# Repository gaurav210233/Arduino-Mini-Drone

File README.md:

# Arduino-Mini-Drone

## Breakout Boards
* Arduino Pro Mini ATMEGA328P 5V/16M - https://robu.in/product/atmega328p-pro-mini-5v-16mhz-compatible-with-arduino/
* GY-91 MPU9250+BMP280 10DOF Acceleration Gyro 9-Axis Sensor Module - https://robu.in/product/gy-91-mpu9250bmp280-10dof-acceleration-gyro-9-axis-sensor-module/
* M177 NRF24L01 2.4GHz Antenna Wireless Transceiver Module - https://robu.in/product/m177-nrf24l01-2-4ghz-antenna-wireless-transceiver-module/

## Libraries
* Bolder Flight Systems MPU9250 - https://github.com/bolderflight/invensense-imu
* Adafruit_BMP280_Library - https://github.com/adafruit/Adafruit_BMP280_Library
* RF24 - https://github.com/nRF24/RF24

## Useful Links
* Interactive BOM V2 - https://gaurav210233.github.io/Arduino-Mini-Drone/Arduino-Mini-Drone-KiCad/V2/bom/ibom.html
* Interactive BOM V2-ESC - https://gaurav210233.github.io/Arduino-Mini-Drone/Arduino-Mini-Drone-KiCad/V2-ESC/bom/ibom.html
* Interactive BOM V2-FC - https://gaurav210233.github.io/Arduino-Mini-Drone/Arduino-Mini-Drone-KiCad/V2-FC/bom/ibom.html

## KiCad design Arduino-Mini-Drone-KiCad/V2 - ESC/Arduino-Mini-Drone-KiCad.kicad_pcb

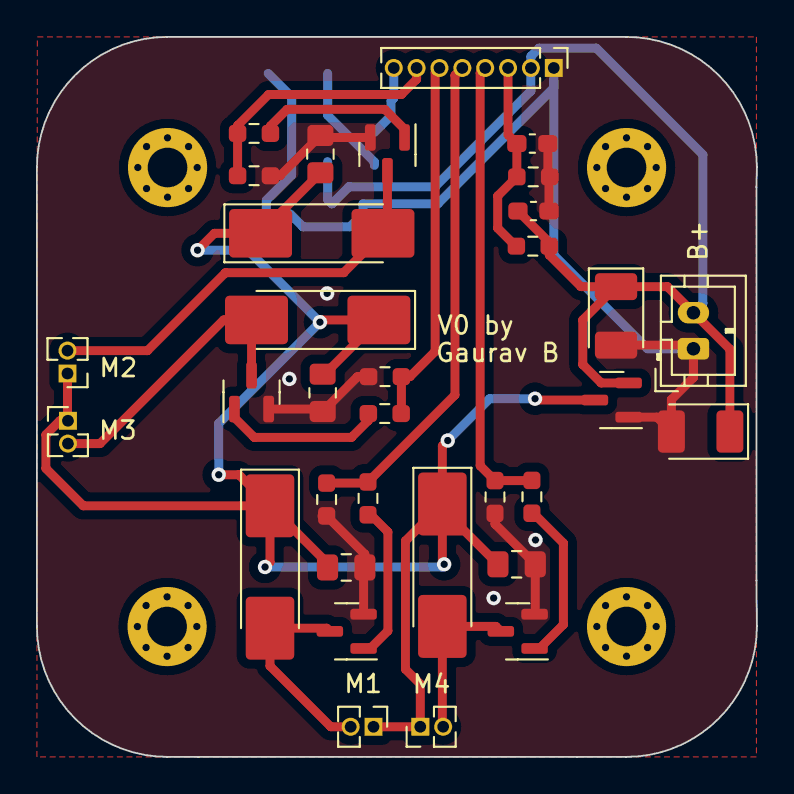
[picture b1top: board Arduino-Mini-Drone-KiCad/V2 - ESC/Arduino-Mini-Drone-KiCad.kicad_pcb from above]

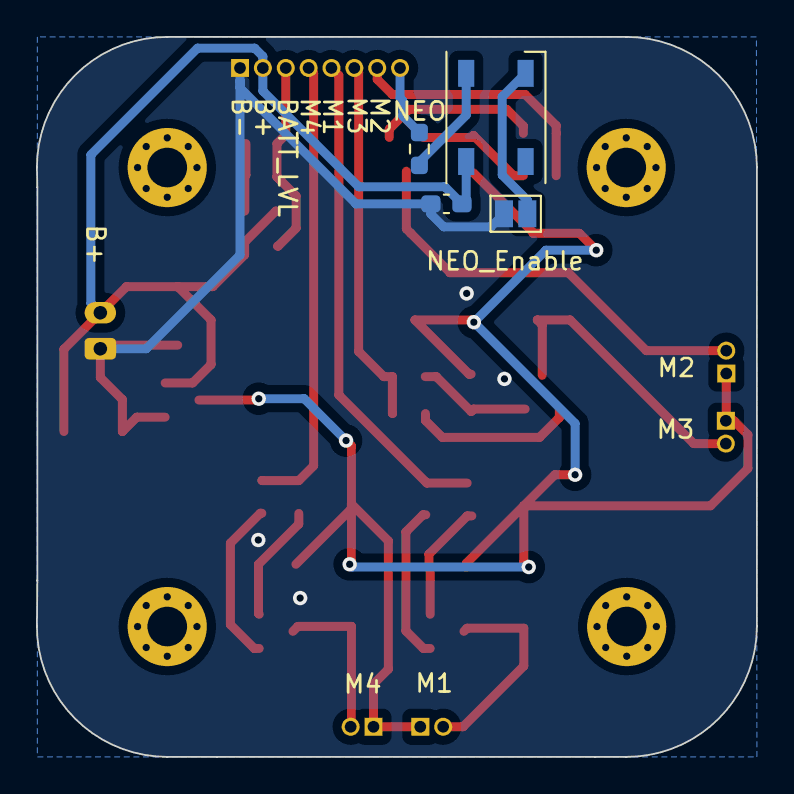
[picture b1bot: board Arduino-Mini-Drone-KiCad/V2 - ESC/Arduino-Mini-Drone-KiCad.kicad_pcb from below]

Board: 2 copper layers, 40.0 x 40.0 mm, 41 parts (4 on the bottom side), 19 nets.

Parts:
B+: PWR; JST_PH_B2B-PH-K_1x02_P2.00mm_Vertical
C10, C11, C12, C13: 22uf; C_0805_2012Metric_Pad1.18x1.45mm_HandSolder
C14, C15: 100uf; CP_EIA-3528-12_Kemet-T_Pad1.50x2.35mm_HandSolder
C17: 10uf; C_0603_1608Metric_Pad1.08x0.95mm_HandSolder
C18, C19: 100nf; C_0603_1608Metric_Pad1.08x0.95mm_HandSolder
D3, D4, D5, D6: SS34; D_MELF_Handsoldering
D9: WS2812B; LED_WS2812B_PLCC4_5.0x5.0mm_P3.2mm
H5, H6, H7, H8: MountingHole; MountingHole_2.2mm_M2_Pad_Via
M1: Motor1; PinHeader_1x02_P1.27mm_Vertical
M2: Motor2; PinHeader_1x02_P1.27mm_Vertical
M3: Motor3; PinHeader_1x02_P1.27mm_Vertical
M4: Motor4; PinHeader_1x02_P1.27mm_Vertical
NEO: POWER; PinHeader_1x08_P1.27mm_Vertical
NEO_Enable: LED ON OFF; SolderJumper-2_P1.3mm_Open_Pad1.0x1.5mm
Q1, Q2, Q3, Q4: AO3400A; SOT-23
Q5: AO3401A; SOT-23
R4, R6, R8, R10: 10k; R_0603_1608Metric_Pad0.98x0.95mm_HandSolder
R5, R7, R9, R11: 100; R_0603_1608Metric_Pad0.98x0.95mm_HandSolder
R12: 100k; R_0603_1608Metric_Pad0.98x0.95mm_HandSolder
R13: 33k; R_0603_1608Metric_Pad0.98x0.95mm_HandSolder
R14: 390; R_0603_1608Metric_Pad0.98x0.95mm_HandSolder

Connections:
+BATT: B+.2, C14.1, C15.1, C17.2, C19.2, D9.1 (VDD), NEO.2, Q5.2 (S), R12.1
-BATT: B+.1, C10.1, C11.1, C12.1, C13.1, C14.2, C15.2, C17.1, C18.1, C19.1, NEO.1, NEO_Enable.2 (B), Q1.2 (S), Q2.2 (S), Q3.2 (S), Q4.2 (S), Q5.1 (G), R4.1, R6.1, R8.1, R10.1, R13.2
BATT LVL: C18.2, NEO.3, R12.2, R13.1
D4 IN: NEO.8, R14.1
M1: NEO.5, R4.2, R5.2
M2: NEO.7, R6.2, R7.2
M3: NEO.6, R8.2, R9.2
M4: NEO.4, R10.2, R11.2
unnamed: D3.2 (A), M1.2, Q1.3 (D)
unnamed: D4.2 (A), M2.2, Q2.3 (D)
unnamed: D5.2 (A), M3.2, Q3.3 (D)
unnamed: D6.2 (A), M4.2, Q4.3 (D)
unnamed: D9.4 (DIN), R14.2
unnamed: D9.3 (VSS), NEO_Enable.1 (A)
unnamed: Q1.1 (G), R5.1
unnamed: Q2.1 (G), R7.1
unnamed: Q3.1 (G), R9.1
unnamed: Q4.1 (G), R11.1
VMOT: C10.2, C11.2, C12.2, C13.2, D3.1 (K), D4.1 (K), D5.1 (K), D6.1 (K), M1.1, M2.1, M3.1, M4.1, Q5.3 (D)

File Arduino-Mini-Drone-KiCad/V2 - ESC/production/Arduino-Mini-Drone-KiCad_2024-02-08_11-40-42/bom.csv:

Designator,Footprint,Quantity,Value,LCSC Part #
B+,JST_PH_B2B-PH-K_1x02_P2.00mm_Vertical,1,PWR,
"C10, C11, C12, C13",0805,4,22uf,C109447
"C14, C15",CP_EIA-3528-12_Kemet-T_Pad1.50x2.35mm_HandSolder,2,100uf,C171664
C17,0603,1,10uf,C380316
"C18, C19",0603,2,100nf,C14663
"D3, D4, D5, D6",D_MELF_Handsoldering,4,SS34,C3011102
D9,LED_WS2812B_PLCC4_5.0x5.0mm_P3.2mm,1,WS2812B,C2761795
"H5, H6, H7, H8",MountingHole_2.2mm_M2_Pad_Via,4,MountingHole,
M1,PinHeader_1x02_P1.27mm_Vertical,1,Motor1,
M2,PinHeader_1x02_P1.27mm_Vertical,1,Motor2,
M3,PinHeader_1x02_P1.27mm_Vertical,1,Motor3,
M4,PinHeader_1x02_P1.27mm_Vertical,1,Motor4,
NEO,PinHeader_1x08_P1.27mm_Vertical,1,POWER,
NEO_Enable,SolderJumper-2_P1.3mm_Open_Pad1.0x1.5mm,1,LED ON OFF,
"Q1, Q2, Q3, Q4",SOT-23,4,AO3400A,C347475
Q5,SOT-23,1,AO3401A,C347476
"R10, R4, R6, R8",0603,4,10k,C25804
"R11, R5, R7, R9",0603,4,100,C19702
R12,0603,1,100k,C25803
R13,0603,1,33k,C4216
R14,0603,1,390,C23151

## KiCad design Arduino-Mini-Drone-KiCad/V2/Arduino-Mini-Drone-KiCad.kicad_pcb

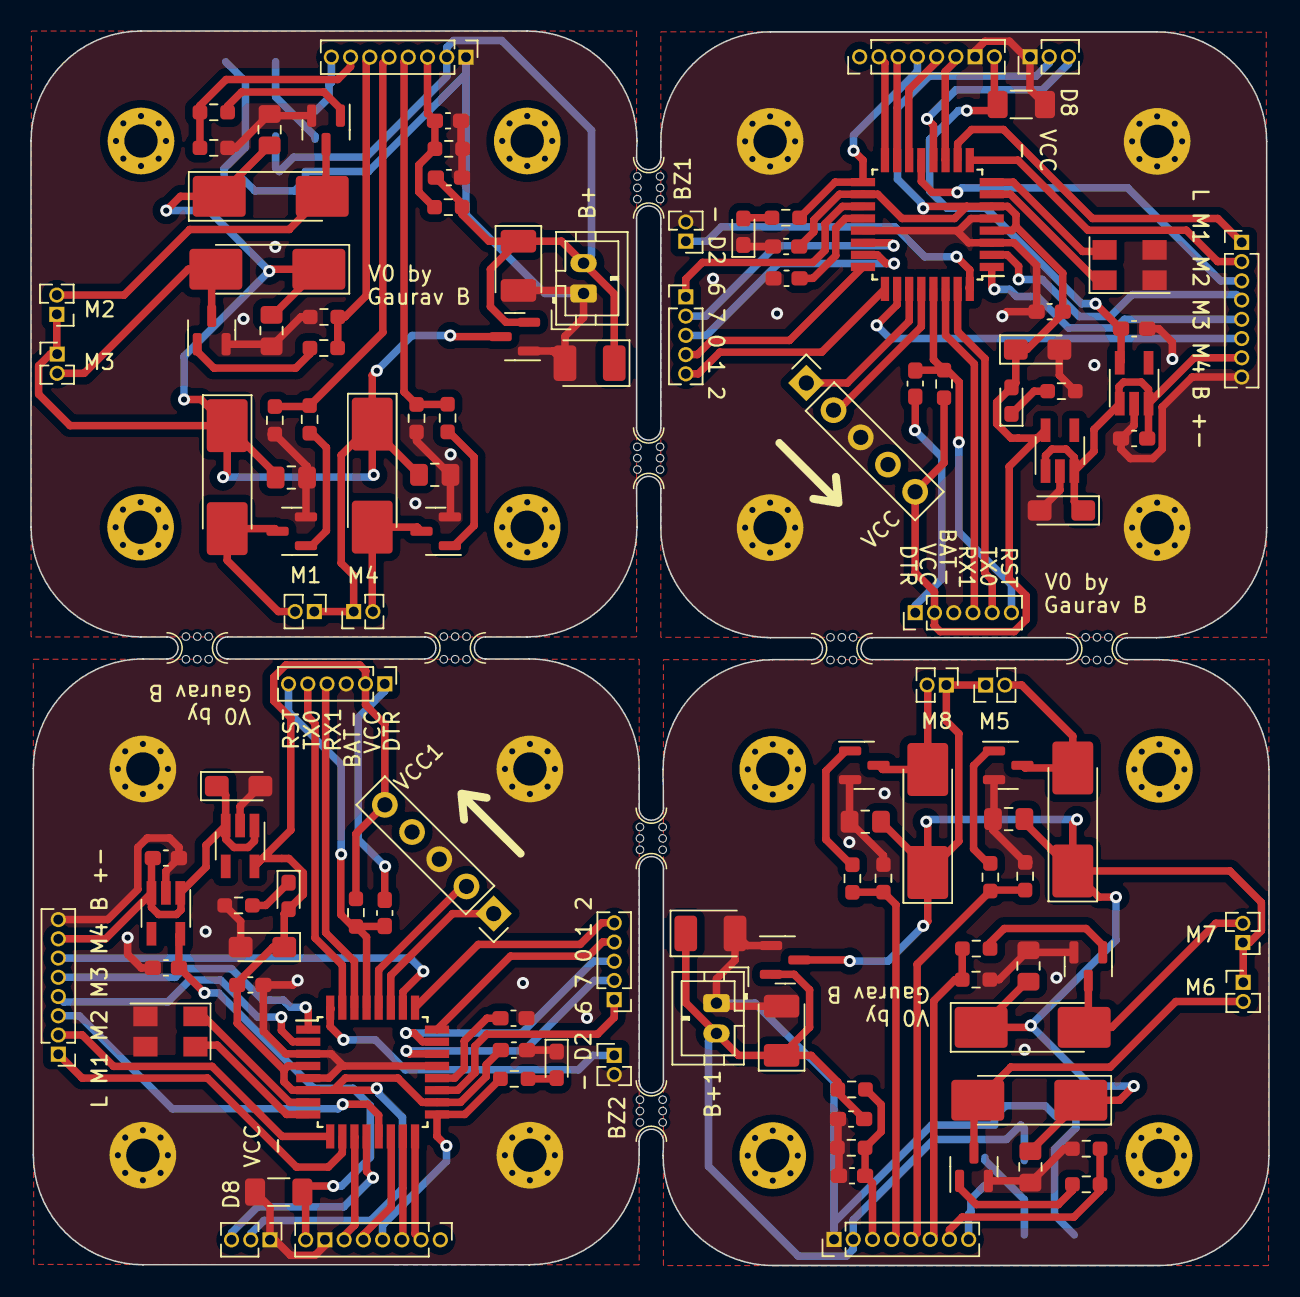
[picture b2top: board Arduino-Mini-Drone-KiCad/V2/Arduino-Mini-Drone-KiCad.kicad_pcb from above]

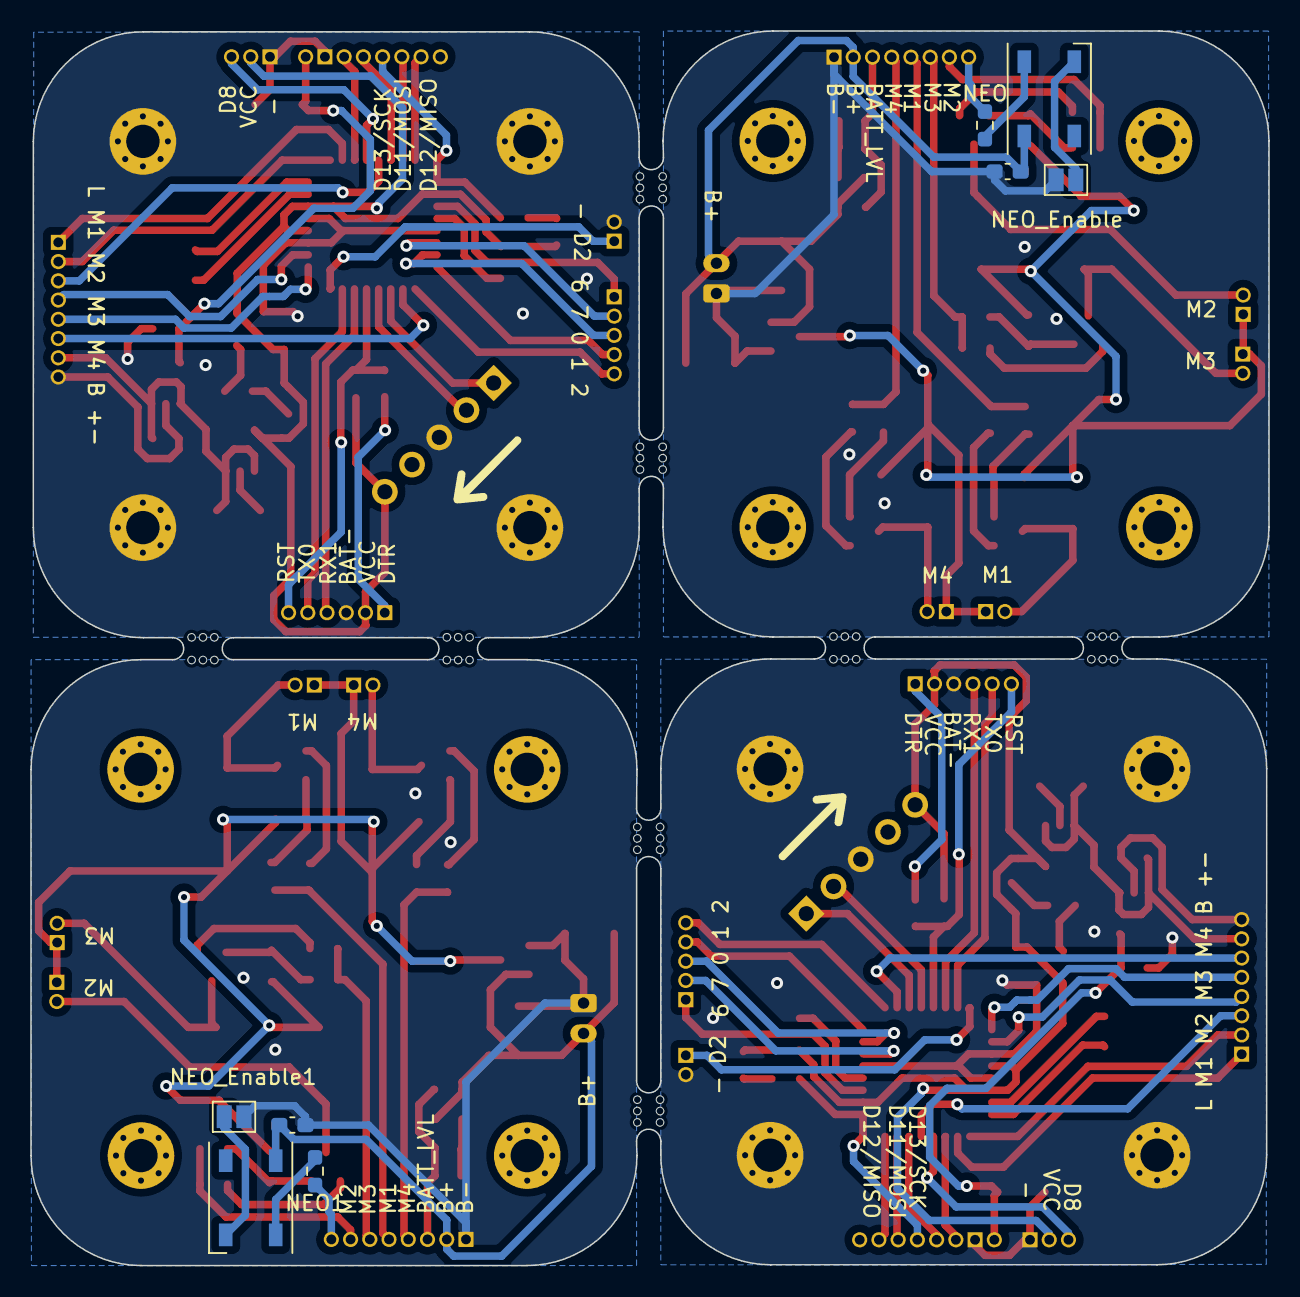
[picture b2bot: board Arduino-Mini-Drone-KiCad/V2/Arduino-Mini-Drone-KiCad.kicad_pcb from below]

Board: 2 copper layers, 81.7 x 81.5 mm, 148 parts (8 on the bottom side), 51 nets.

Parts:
B+, B+1: PWR; JST_PH_B2B-PH-K_1x02_P2.00mm_Vertical
BZ1, BZ2: Buzzer; PinHeader_1x02_P1.27mm_Vertical
C1, C2, C3, C6, C16, C20, C21, C24: 0.1uf; C_0603_1608Metric_Pad1.08x0.95mm_HandSolder
C4, C5, C22, C23: 10uf; CP_EIA-3216-10_Kemet-I_Pad1.58x1.35mm_HandSolder
C7, C8, C25, C26: 1uf; C_0603_1608Metric_Pad1.08x0.95mm_HandSolder
C9, C27: 10uf; C_1206_3216Metric_Pad1.33x1.80mm_HandSolder
C10, C11, C12, C13, C28, C29, C30, C31: 22uf; C_0805_2012Metric_Pad1.18x1.45mm_HandSolder
C14, C15, C32, C33: 100uf; CP_EIA-3528-12_Kemet-T_Pad1.50x2.35mm_HandSolder
C17, C34: 10uf; C_0603_1608Metric_Pad1.08x0.95mm_HandSolder
C18, C19, C35, C36: 100nf; C_0603_1608Metric_Pad1.08x0.95mm_HandSolder
D1, D7: Green; LED_0603_1608Metric_Pad1.05x0.95mm_HandSolder
D2, D8: Red; LED_0603_1608Metric_Pad1.05x0.95mm_HandSolder
D3, D4, D5, D6, D10, D11, D12, D13: SS34; D_MELF_Handsoldering
D9, D14: WS2812B; LED_WS2812B_PLCC4_5.0x5.0mm_P3.2mm
H1, H2, H3, H4, H5, H6, H7, H8, H9, H10, H11, H12, H13, H14, H15, H16: MountingHole; MountingHole_2.2mm_M2_Pad_Via
J1, J3: NRF24; PinHeader_1x08_P1.27mm_Vertical
J2, J4: UART + BT; PinHeader_1x06_P1.27mm_Vertical
J7, J8: MCU; PinHeader_1x08_P1.27mm_Vertical
J11, J12: PPM; PinHeader_1x03_P1.27mm_Vertical
J13, J14: Open; PinHeader_1x05_P1.27mm_Vertical
M1, M5: Motor1; PinHeader_1x02_P1.27mm_Vertical
M2, M6: Motor2; PinHeader_1x02_P1.27mm_Vertical
M3, M7: Motor3; PinHeader_1x02_P1.27mm_Vertical
M4, M8: Motor4; PinHeader_1x02_P1.27mm_Vertical
NEO, NEO1: POWER; PinHeader_1x08_P1.27mm_Vertical
NEO_Enable, NEO_Enable1: LED ON OFF; SolderJumper-2_P1.3mm_Open_Pad1.0x1.5mm
Q1, Q2, Q3, Q4, Q6, Q7, Q8, Q9: AO3400A; SOT-23
Q5, Q10: AO3401A; SOT-23
R1, R15: 10K; R_0603_1608Metric_Pad0.98x0.95mm_HandSolder
R2, R16: 330; R_0603_1608Metric_Pad0.98x0.95mm_HandSolder
R3, R4, R6, R8, R10, R17, R18, R20, R22, R24: 10k; R_0603_1608Metric_Pad0.98x0.95mm_HandSolder
R5, R7, R9, R11, R19, R21, R23, R25: 100; R_0603_1608Metric_Pad0.98x0.95mm_HandSolder
R12, R26: 100k; R_0603_1608Metric_Pad0.98x0.95mm_HandSolder
R13, R27: 33k; R_0603_1608Metric_Pad0.98x0.95mm_HandSolder
R14, R28: 390; R_0603_1608Metric_Pad0.98x0.95mm_HandSolder
U1, U4: ATmega328P-A; TQFP-32_7x7mm_P0.8mm
U2, U5: MIC5205YM5; SOT-23-5_HandSoldering
U3, U6: LP5907MFX-3.3; SOT-23-5_HandSoldering
VCC, VCC1: MPU9250 + BMP280; PinSocket_1x05_P2.54mm_Vertical
Y1, Y2: Crystal_GND2; Crystal_SMD_5032-4Pin_5.0x3.2mm
mouse-bite-2mm-slot, mouse-bite-2mm-slot1, mouse-bite-2mm-slot1#2, mouse-bite-2mm-slot1#3, mouse-bite-2mm-slot1#4, mouse-bite-2mm-slot1#5, mouse-bite-2mm-slot1#6, mouse-bite-2mm-slot#2: VAL**; mouse-bite-2mm-slot

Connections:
+3.3V: C8.2, C9.1, C26.2, C27.1, J1.8, J3.8, U3.5 (OUT), U6.5 (OUT)
+BATT: B+.2, B+1.2, C14.1, C15.1, C17.2, C19.2, C32.1, C33.1, C34.2, C36.2, D9.1 (VDD), D14.1 (VDD), NEO.2, NEO1.2, Q5.2 (S), Q10.2 (S), R12.1, R26.1
+BATT IN: C4.1, C7.2, C22.1, C25.2, J7.7, J8.7, U2.1 (IN), U2.3 (EN), U3.1 (IN), U3.3 (EN), U5.1 (IN), U5.3 (EN), U6.1 (IN), U6.3 (EN)
-BATT: B+.1, B+1.1, BZ1.2 (-), BZ2.2 (-), C2.1, C3.1, C4.2, C5.2, C6.1, C7.1, C8.1, C9.2, C10.1, C11.1, C12.1, C13.1, C14.2, C15.2, C17.1, C18.1, C19.1, C20.1, C21.1, C22.2, C23.2, C24.1, C25.1, C26.1, C27.2, C28.1, C29.1, C30.1, C31.1, C32.2, C33.2, C34.1, C35.1, C36.1, D1.1 (K), D7.1 (K), H1.1, H2.1, H3.1, H4.1, H9.1, H10.1, H11.1, H12.1, J1.7, J2.3, J3.7, J4.3, J7.8, J8.8, J11.1, J12.1, NEO.1, NEO1.1, NEO_Enable.2 (B), NEO_Enable1.2 (B), Q1.2 (S), Q2.2 (S), Q3.2 (S), Q4.2 (S), Q5.1 (G), Q6.2 (S), Q7.2 (S), Q8.2 (S), Q9.2 (S), Q10.1 (G), R3.1, R4.1, R6.1, R8.1, R10.1, R13.2, R17.1, R18.1, R20.1, R22.1, R24.1, R27.2, U1.3 (GND), U1.5 (GND), U1.21 (GND), U2.2 (GND), U3.2 (GND), U4.3 (GND), U4.5 (GND), U4.21 (GND), U5.2 (GND), U6.2 (GND), VCC.3, VCC1.3, Y1.2, Y1.3, Y2.2, Y2.3
A0: J13.3, J14.3, U1.23 (PC0), U4.23 (PC0)
A1: J13.4, J14.4, U1.24 (PC1), U4.24 (PC1)
A2: J13.5, J14.5, U1.25 (PC2), U4.25 (PC2)
A3: J7.6, J8.6, U1.26 (PC3), U4.26 (PC3)
A4: U1.27 (PC4), U4.27 (PC4), VCC.1, VCC1.1
A5: U1.28 (PC5), U4.28 (PC5), VCC.2, VCC1.2
A6: J13.1, J14.1, U1.19 (ADC6), U4.19 (ADC6)
A7: J13.2, J14.2, U1.22 (ADC7), U4.22 (ADC7)
BATT LVL: C18.2, C35.2, NEO.3, NEO1.3, R12.2, R13.1, R26.2, R27.1
D2: BZ1.1 (+), BZ2.1 (+), U1.32 (PD2), U4.32 (PD2)
D3: J7.5, J8.5, U1.1 (PD3), U4.1 (PD3)
D4: J7.4, J8.4, U1.2 (PD4), U4.2 (PD4)
D4 IN: NEO.8, NEO1.8, R14.1, R28.1
D5: J7.2, J8.2, U1.9 (PD5), U4.9 (PD5)
D6: J7.1, J8.1, U1.10 (PD6), U4.10 (PD6)
D7: J1.6, J3.6, U1.11 (PD7), U4.11 (PD7)
D8: J11.3, J12.3, U1.12 (PB0), U4.12 (PB0)
D9: J7.3, J8.3, U1.13 (PB1), U4.13 (PB1)
D10: J1.5, J3.5, U1.14 (PB2), U4.14 (PB2)
D11: J1.3, J3.3, U1.15 (PB3), U4.15 (PB3)
D12: J1.2, J3.2, U1.16 (PB4), U4.16 (PB4)
D13: J1.4, J3.4, R2.2, R16.2, U1.17 (PB5), U4.17 (PB5)
DTR: C1.2, C16.2, J2.1, J4.1
M1: NEO.5, NEO1.5, R4.2, R5.2, R18.2, R19.2
M2: NEO.7, NEO1.7, R6.2, R7.2, R20.2, R21.2
M3: NEO.6, NEO1.6, R8.2, R9.2, R22.2, R23.2
M4: NEO.4, NEO1.4, R10.2, R11.2, R24.2, R25.2
unnamed: D1.2 (A), D7.2 (A), R2.1, R16.1
unnamed: D2.1 (K), D8.1 (K), R3.2, R17.2
unnamed: D3.2 (A), D10.2 (A), M1.2, M5.2, Q1.3 (D), Q6.3 (D)
unnamed: D4.2 (A), D11.2 (A), M2.2, M6.2, Q2.3 (D), Q7.3 (D)
unnamed: D5.2 (A), D12.2 (A), M3.2, M7.2, Q3.3 (D), Q8.3 (D)
unnamed: D6.2 (A), D13.2 (A), M4.2, M8.2, Q4.3 (D), Q9.3 (D)
unnamed: D9.4 (DIN), D14.4 (DIN), R14.2, R28.2
unnamed: D9.3 (VSS), D14.3 (VSS), NEO_Enable.1 (A), NEO_Enable1.1 (A)
unnamed: Q1.1 (G), Q6.1 (G), R5.1, R19.1
unnamed: Q2.1 (G), Q7.1 (G), R7.1, R21.1
unnamed: Q3.1 (G), Q8.1 (G), R9.1, R23.1
unnamed: Q4.1 (G), Q9.1 (G), R11.1, R25.1
unnamed: C2.2, C20.2, U1.20 (AREF), U4.20 (AREF)
unnamed: U1.7 (XTAL1/PB6), U4.7 (XTAL1/PB6), Y1.1, Y2.1
unnamed: U1.8 (XTAL2/PB7), U4.8 (XTAL2/PB7), Y1.4, Y2.4
RST: C1.1, C16.1, J2.6, J4.6, R1.1, R15.1, U1.29 (~RESET/PC6), U4.29 (~RESET/PC6)
RX1: J2.4, J4.4, U1.30 (PD0), U4.30 (PD0)
TX0: J2.5, J4.5, U1.31 (PD1), U4.31 (PD1)
VCC: C3.2, C5.1, C6.2, C21.2, C23.1, C24.2, D2.2 (A), D8.2 (A), J2.2, J4.2, J11.2, J12.2, R1.2, R15.2, U1.4 (VCC), U1.6 (VCC), U1.18 (AVCC), U2.5 (OUT), U4.4 (VCC), U4.6 (VCC), U4.18 (AVCC), U5.5 (OUT), VCC.5, VCC1.5
VMOT: C10.2, C11.2, C12.2, C13.2, C28.2, C29.2, C30.2, C31.2, D3.1 (K), D4.1 (K), D5.1 (K), D6.1 (K), D10.1 (K), D11.1 (K), D12.1 (K), D13.1 (K), M1.1, M2.1, M3.1, M4.1, M5.1, M6.1, M7.1, M8.1, Q5.3 (D), Q10.3 (D)

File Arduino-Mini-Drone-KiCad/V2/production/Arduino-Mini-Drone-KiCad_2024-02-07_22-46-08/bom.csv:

Designator,Footprint,Quantity,Value,LCSC Part #
"B+, B+1",JST_PH_B2B-PH-K_1x02_P2.00mm_Vertical,2,PWR,
"BZ1, BZ2",PinHeader_1x02_P1.27mm_Vertical,2,Buzzer,
"C1, C16, C2, C20, C21, C24, C3, C6",0603,8,0.1uf,C71629
"C10, C11, C12, C13, C28, C29, C30, C31",0805,8,22uf,C109447
"C14, C15, C32, C33",CP_EIA-3528-12_Kemet-T_Pad1.50x2.35mm_HandSolder,4,100uf,C171664
"C17, C34",0603,2,10uf,C380316
"C18, C19, C35, C36",0603,4,100nf,C14663
"C22, C23, C4, C5",CP_EIA-3216-10_Kemet-I_Pad1.58x1.35mm_HandSolder,4,10uf,C600516
"C25, C26, C7, C8",0603,4,1uf,C15849
"C27, C9",1206,2,10uf,C600516
"D1, D7",0603,2,Green,C241891
"D10, D11, D12, D13, D3, D4, D5, D6",D_MELF_Handsoldering,8,SS34,C3011102
"D14, D9",LED_WS2812B_PLCC4_5.0x5.0mm_P3.2mm,2,WS2812B,C2761795
"D2, D8",0603,2,Red,C266784
"H1, H10, H11, H12, H13, H14, H15, H16, H2, H3, H4, H5, H6, H7, H8, H9",MountingHole_2.2mm_M2_Pad_Via,16,MountingHole,
"J1, J3",PinHeader_1x08_P1.27mm_Vertical,2,NRF24,
"J11, J12",PinHeader_1x03_P1.27mm_Vertical,2,PPM,
"J13, J14",PinHeader_1x05_P1.27mm_Vertical,2,Open,
"J2, J4",PinHeader_1x06_P1.27mm_Vertical,2,UART + BT,
"J7, J8",PinHeader_1x08_P1.27mm_Vertical,2,MCU,
"M1, M5",PinHeader_1x02_P1.27mm_Vertical,2,Motor1,
"M2, M6",PinHeader_1x02_P1.27mm_Vertical,2,Motor2,
"M3, M7",PinHeader_1x02_P1.27mm_Vertical,2,Motor3,
"M4, M8",PinHeader_1x02_P1.27mm_Vertical,2,Motor4,
"NEO, NEO1",PinHeader_1x08_P1.27mm_Vertical,2,POWER,
"NEO_Enable, NEO_Enable1",SolderJumper-2_P1.3mm_Open_Pad1.0x1.5mm,2,LED ON OFF,
"Q1, Q2, Q3, Q4, Q6, Q7, Q8, Q9",SOT-23,8,AO3400A,C347475
"Q10, Q5",SOT-23,2,AO3401A,C347476
"R1, R10, R15, R17, R18, R20, R22, R24, R3, R4, R6, R8",0603,12,10K,C25804
"R11, R19, R21, R23, R25, R5, R7, R9",0603,8,100,C19702
"R12, R26",0603,2,100k,C25803
"R13, R27",0603,2,33k,C4216
"R14, R28",0603,2,390,C23151
"R16, R2",0603,2,330,C23140
"U1, U4",TQFP-32_7x7mm_P0.8mm,2,ATmega328P-A,C14877
"U2, U5",SOT-23-5_HandSoldering,2,MIC5205YM5,C412820
"U3, U6",SOT-23-5_HandSoldering,2,LP5907MFX-3.3,C5370990
"VCC, VCC1",PinSocket_1x05_P2.54mm_Vertical,2,MPU9250 + BMP280,
"Y1, Y2",Crystal_SMD_5032-4Pin_5.0x3.2mm,2,Crystal_GND2,C124318
"mouse-bite-2mm-slot_2, mouse-bite-2mm-slot, mouse-bite-2mm-slot1_6, mouse-bite-2mm-slot1_5, mouse-bite-2mm-slot1_4, mouse-bite-2mm-slot1_3, mouse-bite-2mm-slot1_2, mouse-bite-2mm-slot1",mouse-bite-2mm-slot,8,VAL**,

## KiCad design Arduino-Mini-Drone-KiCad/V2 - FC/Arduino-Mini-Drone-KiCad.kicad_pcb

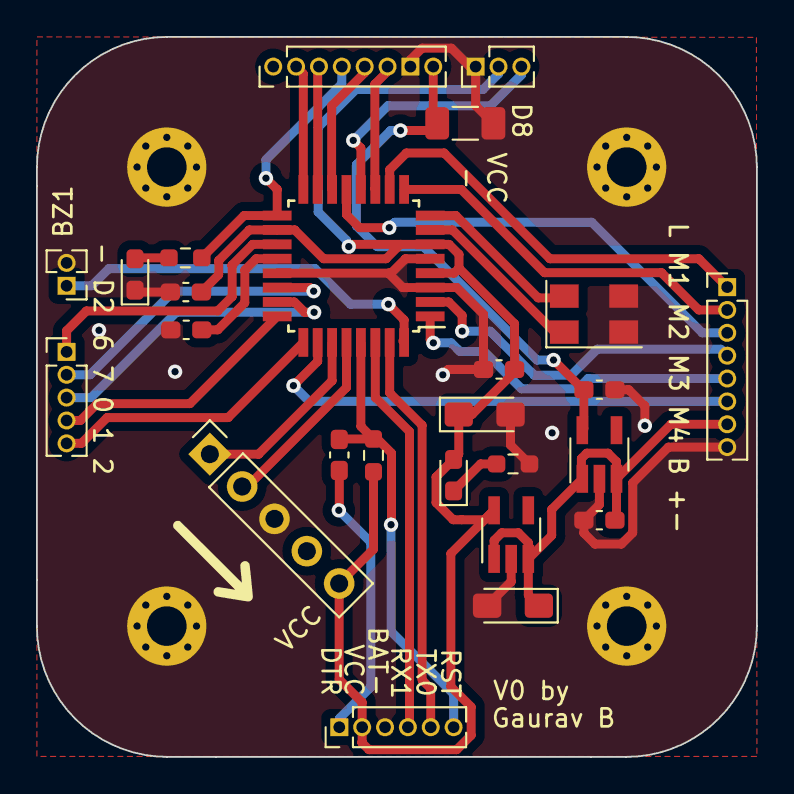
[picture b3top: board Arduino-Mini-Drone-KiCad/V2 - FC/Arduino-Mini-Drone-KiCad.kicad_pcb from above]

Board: 2 copper layers, 40.0 x 40.0 mm, 29 parts (0 on the bottom side), 33 nets.

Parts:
BZ1: Buzzer; PinHeader_1x02_P1.27mm_Vertical
C1, C2, C3, C6: 0.1uf; C_0603_1608Metric_Pad1.08x0.95mm_HandSolder
C4, C5: 10uf; CP_EIA-3216-10_Kemet-I_Pad1.58x1.35mm_HandSolder
C7, C8: 1uf; C_0603_1608Metric_Pad1.08x0.95mm_HandSolder
C9: 10uf; C_1206_3216Metric_Pad1.33x1.80mm_HandSolder
D1: Green; LED_0603_1608Metric_Pad1.05x0.95mm_HandSolder
D2: Red; LED_0603_1608Metric_Pad1.05x0.95mm_HandSolder
H1, H2, H3, H4: MountingHole; MountingHole_2.2mm_M2_Pad_Via
J1: NRF24; PinHeader_1x08_P1.27mm_Vertical
J2: UART + BT; PinHeader_1x06_P1.27mm_Vertical
J7: MCU; PinHeader_1x08_P1.27mm_Vertical
J11: PPM; PinHeader_1x03_P1.27mm_Vertical
J13: Open; PinHeader_1x05_P1.27mm_Vertical
R1: 10K; R_0603_1608Metric_Pad0.98x0.95mm_HandSolder
R2: 330; R_0603_1608Metric_Pad0.98x0.95mm_HandSolder
R3: 10k; R_0603_1608Metric_Pad0.98x0.95mm_HandSolder
U1: ATmega328P-A; TQFP-32_7x7mm_P0.8mm
U2: MIC5205YM5; SOT-23-5_HandSoldering
U3: LP5907MFX-3.3; SOT-23-5_HandSoldering
VCC: MPU9250 + BMP280; PinSocket_1x05_P2.54mm_Vertical
Y1: Crystal_GND2; Crystal_SMD_5032-4Pin_5.0x3.2mm

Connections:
+3.3V: C8.2, C9.1, J1.8, U3.5 (OUT)
+BATT IN: C4.1, C7.2, J7.7, U2.1 (IN), U2.3 (EN), U3.1 (IN), U3.3 (EN)
-BATT: BZ1.2 (-), C2.1, C3.1, C4.2, C5.2, C6.1, C7.1, C8.1, C9.2, D1.1 (K), H1.1, H2.1, H3.1, H4.1, J1.7, J2.3, J7.8, J11.1, R3.1, U1.3 (GND), U1.5 (GND), U1.21 (GND), U2.2 (GND), U3.2 (GND), VCC.3, Y1.2, Y1.3
A0: J13.3, U1.23 (PC0)
A1: J13.4, U1.24 (PC1)
A2: J13.5, U1.25 (PC2)
A3: J7.6, U1.26 (PC3)
A4: U1.27 (PC4), VCC.1
A5: U1.28 (PC5), VCC.2
A6: J13.1, U1.19 (ADC6)
A7: J13.2, U1.22 (ADC7)
D2: BZ1.1 (+), U1.32 (PD2)
D3: J7.5, U1.1 (PD3)
D4: J7.4, U1.2 (PD4)
D5: J7.2, U1.9 (PD5)
D6: J7.1, U1.10 (PD6)
D7: J1.6, U1.11 (PD7)
D8: J11.3, U1.12 (PB0)
D9: J7.3, U1.13 (PB1)
D10: J1.5, U1.14 (PB2)
D11: J1.3, U1.15 (PB3)
D12: J1.2, U1.16 (PB4)
D13: J1.4, R2.2, U1.17 (PB5)
DTR: C1.2, J2.1
unnamed: D1.2 (A), R2.1
unnamed: D2.1 (K), R3.2
unnamed: C2.2, U1.20 (AREF)
unnamed: U1.7 (XTAL1/PB6), Y1.1
unnamed: U1.8 (XTAL2/PB7), Y1.4
RST: C1.1, J2.6, R1.1, U1.29 (~RESET/PC6)
RX1: J2.4, U1.30 (PD0)
TX0: J2.5, U1.31 (PD1)
VCC: C3.2, C5.1, C6.2, D2.2 (A), J2.2, J11.2, R1.2, U1.4 (VCC), U1.6 (VCC), U1.18 (AVCC), U2.5 (OUT), VCC.5

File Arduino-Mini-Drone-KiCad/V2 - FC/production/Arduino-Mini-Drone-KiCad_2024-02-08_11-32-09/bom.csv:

Designator,Footprint,Quantity,Value,LCSC Part #
BZ1,PinHeader_1x02_P1.27mm_Vertical,1,Buzzer,
"C1, C2, C3, C6",0603,4,0.1uf,C71629
"C4, C5",CP_EIA-3216-10_Kemet-I_Pad1.58x1.35mm_HandSolder,2,10uf,C600516
"C7, C8",0603,2,1uf,C15849
C9,1206,1,10uf,C600516
D1,0603,1,Green,C241891
D2,0603,1,Red,C266784
"H1, H2, H3, H4",MountingHole_2.2mm_M2_Pad_Via,4,MountingHole,
J1,PinHeader_1x08_P1.27mm_Vertical,1,NRF24,
J11,PinHeader_1x03_P1.27mm_Vertical,1,PPM,
J13,PinHeader_1x05_P1.27mm_Vertical,1,Open,
J2,PinHeader_1x06_P1.27mm_Vertical,1,UART + BT,
J7,PinHeader_1x08_P1.27mm_Vertical,1,MCU,
"R1, R3",0603,2,10K,C25804
R2,0603,1,330,C23140
U1,TQFP-32_7x7mm_P0.8mm,1,ATmega328P-A,C14877
U2,SOT-23-5_HandSoldering,1,MIC5205YM5,C412820
U3,SOT-23-5_HandSoldering,1,LP5907MFX-3.3,C5370990
VCC,PinSocket_1x05_P2.54mm_Vertical,1,MPU9250 + BMP280,
Y1,Crystal_SMD_5032-4Pin_5.0x3.2mm,1,Crystal_GND2,C124318

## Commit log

2024-01-11 initialized pio project
2024-01-11 added some breakout boards to readme
2024-01-11 installed imu and altitude library
2024-01-13 added nrf24 library
2024-01-16 created custom header and helper files
2024-01-17 Added wrapper functions * To initialize bmp * To get - Altitude, Pressure, Temperature Added Comments from original library
2024-01-17 Added wrapper function and comments
2024-01-17 removed gitignore
2024-01-17 fixed
2024-01-17 Added functions to initialize IMU and calibrate magnetometer
2024-01-17 ignored some files
2024-01-17 added functions to read the IMU
2024-01-17 created KiCad files, completed schematics, downloaded Datasheets
2024-01-18 removed invensense mpu9250 library
2024-01-22 added mpu9250 lib & completed PCB layout
2024-01-22 created copy for easy components
2024-01-22 kept backups local
2024-02-06 Completed Panelized PCB in V2 delete Row 2 PCB for error resolution
2024-02-06 added interactive BOM
2024-02-06 Added link to Readme for BOM
2024-02-08 Created Seperate boards for ESC and FC
2024-02-08 Restructured Folders
2024-02-08 Added BOM
2024-02-08 Added Backups
2024-02-13 Restructuring code deleted wrappers
2024-02-14 cleared main
2024-02-16 created custom wrapper headers
2024-02-16 added test functionality for nrf and mpu
2024-02-16 just created file
2024-02-16 implemented nrf functions
